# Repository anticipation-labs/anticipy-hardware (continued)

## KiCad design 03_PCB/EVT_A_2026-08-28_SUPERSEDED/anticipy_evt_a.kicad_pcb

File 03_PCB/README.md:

# 03 — PCB

**NOTHING IN THIS FOLDER MAY BE SENT TO A FABRICATOR AS A PRODUCTION RELEASE.**

There is no released Gerber, ODB++, drill file, pick-and-place or assembly drawing anywhere in
this repository. Three custom boards were started. None were finished. A fourth is specified but
not designed.

## The four revisions

| Folder | Board | State |
|---|---|---|
| `R1_TARGET_NOT_YET_DESIGNED/` | R1 | Empty by design. The brief lives in `../01_CURRENT_TARGET_R1/`. |
| `EVT_A_2026-08-28_SUPERSEDED/` | `anticipy_evt_a`, 37.5 × 14 mm four-layer, **nRF54L15** | Deliberate fabrication hold: 0 segments, 0 vias, 0 zones. No copper was ever laid, specifically so no misleading Gerbers could exist. Superseded by the R1 brief. |
| `R0B_CHECKPOINT_NOT_FOR_FAB/` | R0B, 45.8 × 18.0 mm four-layer, 0.80 mm | 70 electrical references, 223 pins, **176 connections unrouted**. The master package's headline board. |
| `R0_ROUTING_HISTORY_NOT_FOR_FAB/` | R0 / `ANT-PROD-R0 EVT` | **The furthest-routed board.** 45 of 46 signal nets carry copper. 31 commits of history (v21 → v43) driving unconnected nets from 199 down to 23 non-GND. |

## Read this before touching R0

`R0_ROUTING_HISTORY_NOT_FOR_FAB/` contains a **live `.git` repository with no remote**. Its 31
commits are the only version-controlled hardware history found on the machine, and they existed
nowhere else before this consolidation. It also carries uncommitted changes to `.kicad_pcb` and
`.kicad_pro`, plus an untracked `tools/final_build.py`. These were preserved exactly as found.

It includes `tools/route_board.py` — a purpose-written negotiated-congestion autorouter. That is
weeks of work and it exists only here.

## The R0 ambiguity

There are **two different files both called the R0 board**:

| | Master package copy | This git repository |
|---|---|---|
| `.kicad_pcb` sha256 | `64a4931f0fc455cd…` | `c086bae9fedc9a55…` |
| DRC timestamp | 2026-08-30 02:28:59 | 2026-08-29 18:04:35 |
| DRC violations | 134 | 4 |

The master package's copy was generated later by an automated run (its DRC header references a
sandbox path) and is **less** routed. Establish which is canonical before anyone uploads "R0"
anywhere — especially given the live JLCPCB order, whose email record does not prove which
revision was uploaded.

## Ordering note

`R0` is *more* complete than `R0B`, despite the naming. Either R0B discarded R0's routing work
or the master package's framing is wrong. Nothing on disk explains which.

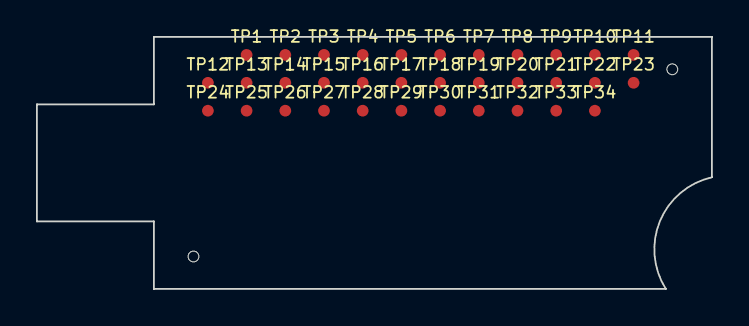
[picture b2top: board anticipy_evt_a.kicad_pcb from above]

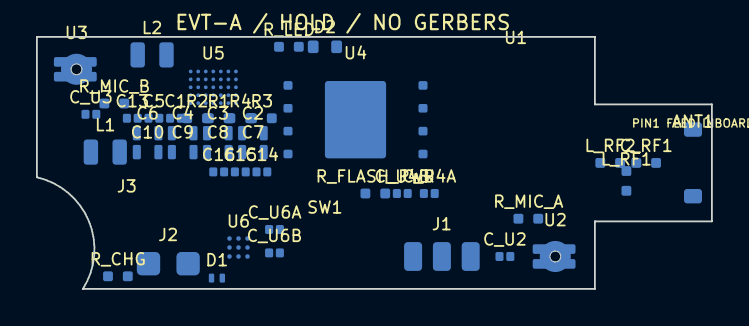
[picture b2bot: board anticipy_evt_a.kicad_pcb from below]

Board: 4 copper layers, 37.5 x 14.0 mm, 81 parts (47 on the bottom side), 38 nets, no tracks yet.

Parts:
ANT1: 2450AT18A0100001E
C1: 1uF/25V; C_OPEN
C2, C3, C4, C7, C8, C9, C10: 10uF; C_OPEN
C5: 1uF; C_OPEN
C6: 2.2uF EMK107BB7225KA-T; C_OPEN
C13: 100nF; C_OPEN
C14, C15, C16: 100nF C0402C104M4RAC7867; C_OPEN
C_RF1: DNP/TUNE (eval 1.0pF); 0402_RF
C_U2, C_U3, C_U4A: 100nF; C_OPEN
C_U4B: 1uF; C_OPEN
C_U6A: 1uF REG; C_OPEN
C_U6B: 1uF VDD; C_OPEN
D1: TPD1E10B06DPYR; X1SON2_DPY
D2: LED MPN OPEN; LED_1608_OPEN
J1: BAT-ANT-200-001 3-wire; BATTERY_WIRE_PADS
J2: MAGNETIC POGO 5V; CHARGE_PADS
J3: JYC720FDRL FPC hot-bar land gate; JYC720FDRL_HOTBAR_LAND_GATE
L1, L2: 2.2uH CIGT201610EH2R2MNE; CIGT201610
L_RF1: DNP/TUNE (eval 2.7nH); 0402_RF
L_RF2: DNP/TUNE (eval 3.9nH); 0402_RF
R1, R2: 10k; R_0402_OPEN
R3: 47k; R_0402_OPEN
R4: 150k; R_0402_OPEN
R_CHG: 0R; R_0402_OPEN
R_FLASH_PWR: 0R; R_0402_OPEN
R_LED: OPEN; R_0402_OPEN
R_MIC_A: 0R; R_0402_OPEN
R_MIC_B: 0R; R_0402_OPEN
SW1: SKSCLCE010; SKSCLCE010_PADMAP_GATE
TP1: GND; TP_0P65
TP2: CHG_5V; TP_0P65
TP3: VBUS; TP_0P65
TP4: VBAT; TP_0P65
TP5: BAT_NTC; TP_0P65
TP6: VSYS; TP_0P65
TP7: 1V8; TP_0P65
TP8: 3V0; TP_0P65
TP9: FLASH_VDD; TP_0P65
TP10: QSPI_CS_TO_U1_PAD_TBD; TP_0P65
TP11: QSPI_CLK_TO_U1_PAD_TBD; TP_0P65
TP12: QSPI_IO0_TO_U1_PAD_TBD; TP_0P65
TP13: QSPI_IO1_TO_U1_PAD_TBD; TP_0P65
TP14: QSPI_IO2_TO_U1_PAD_TBD; TP_0P65
TP15: QSPI_IO3_TO_U1_PAD_TBD; TP_0P65
TP16: PDM_CLK_TO_U1_PAD_TBD; TP_0P65
TP17: PDM_DATA_TO_U1_PAD_TBD; TP_0P65
TP18: MIC_A_VDD; TP_0P65
TP19: MIC_B_VDD; TP_0P65
TP20: PMIC_SDA_TO_U1_PAD_TBD; TP_0P65
TP21: PMIC_SCL_TO_U1_PAD_TBD; TP_0P65
TP22: HAPTIC_SDA_TO_U1_PAD_TBD; TP_0P65
TP23: HAPTIC_SCL_TO_U1_PAD_TBD; TP_0P65
TP24: HAPTIC_EN_TO_U1_PAD_TBD; TP_0P65
TP25: HAPTIC_REG; TP_0P65
TP26: HAPTIC_OUT_P; TP_0P65
TP27: HAPTIC_OUT_M; TP_0P65
TP28: BUTTON_TO_U1_PAD_TBD; TP_0P65
TP29: STATUS_LED_TO_U1_PAD_TBD; TP_0P65
TP30: SWDIO_TO_U1_PAD_TBD; TP_0P65
TP31: SWCLK_TO_U1_PAD_TBD; TP_0P65
TP32: RESET_TO_U1_PAD_TBD; TP_0P65
TP33: UART_TX_TO_U1_PAD_TBD; TP_0P65
TP34: UART_RX_TO_U1_PAD_TBD; TP_0P65
U1: 453-00224R; BL54L15U_PINMAP_GATE
U2, U3: IM69D128S
U4: W25N04KVZEIR; WSON8_8x6_W25N04KV
U5: nPM1300-CAAA; WLCSP35_nPM1300_CAAA
U6: DRV2605LYZFR; DSBGA9_DRV2605L

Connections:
1V8: C7.1, L1.2, TP7.1, U5.B4, U5.B6
3V0: C8.1, C13.1, C_U6B.1, L2.2, R1.1, R2.1, R_FLASH_PWR.1, R_MIC_A.1, R_MIC_B.1, TP8.1, U3.4, U5.B5, U5.C6, U5.E4, U6.C2
BAT_NTC: J1.2, TP5.1, U5.D3
CHG_5V: D1.1, J2.1, R_CHG.1, TP2.1
FLASH_VDD: C_U4A.1, C_U4B.1, R_FLASH_PWR.2, TP9.1, U4.8
GND: C1.2, C2.2, C3.2, C4.2, C5.2, C6.2, C7.2, C8.2, C9.2, C10.2, C13.2, C14.2, C15.2, C16.2, C_U2.2, C_U3.2, C_U4A.2, C_U4B.2, C_U6A.2, C_U6B.2, D1.2, D2.2, J1.3, J2.2, L_RF1.2, R3.2, R4.2, TP1.1, U2.4, U2.5, U3.5, U4.4, U4.9, U5.A6, U5.A7, U5.E7, U6.B1, U6.B3
HAPTIC_EN_TO_U1_PAD_TBD: TP24.1, U6.A1
HAPTIC_OUT_M: TP27.1, U6.C3
HAPTIC_OUT_P: TP26.1, U6.A3
HAPTIC_REG: C_U6A.1, TP25.1, U6.A2
HAPTIC_SCL_TO_U1_PAD_TBD: TP23.1, U6.C1
HAPTIC_SDA_TO_U1_PAD_TBD: TP22.1, U6.B2
LDO1_OUT: C9.1, U5.A4
LDO2_OUT: C10.1, U5.A5
MIC_A_VDD: C_U2.1, R_MIC_A.2, TP18.1, U2.1
MIC_B_VDD: C_U3.1, R_MIC_B.2, TP19.1, U3.1
PDM_CLK_TO_U1_PAD_TBD: TP16.1, U2.2, U3.2
PDM_DATA_TO_U1_PAD_TBD: TP17.1, U2.3, U3.3
PMIC_SCL_TO_U1_PAD_TBD: R2.2, TP21.1, U5.E3
PMIC_SDA_TO_U1_PAD_TBD: R1.2, TP20.1, U5.E5
QSPI_CLK_TO_U1_PAD_TBD: TP11.1, U4.6
QSPI_CS_TO_U1_PAD_TBD: TP10.1, U4.1
QSPI_IO0_TO_U1_PAD_TBD: TP12.1, U4.5
QSPI_IO1_TO_U1_PAD_TBD: TP13.1, U4.2
QSPI_IO2_TO_U1_PAD_TBD: TP14.1, U4.3
QSPI_IO3_TO_U1_PAD_TBD: TP15.1, U4.7
RF_MATCH_A: C_RF1.2, L_RF1.1, L_RF2.1
RF_MATCH_B: ANT1.1, L_RF2.2
STATUS_LED_A: D2.1, R_LED.2
STATUS_LED_TO_U1_PAD_TBD: R_LED.1, TP29.1
SW_BUCK1: L1.1, U5.B7
SW_BUCK2: L2.1, U5.D7
VBAT: C6.1, J1.1, TP4.1, U5.D1, U5.D2
VBUS: C1.1, R_CHG.2, TP3.1, U5.B1, U5.B2
VBUSOUT: C5.1, U5.C3
VSET1: R3.1, U5.E2
VSET2: R4.1, U5.E1
VSYS: C2.1, C3.1, C4.1, C14.1, C15.1, C16.1, TP6.1, U5.C1, U5.C2, U5.C7

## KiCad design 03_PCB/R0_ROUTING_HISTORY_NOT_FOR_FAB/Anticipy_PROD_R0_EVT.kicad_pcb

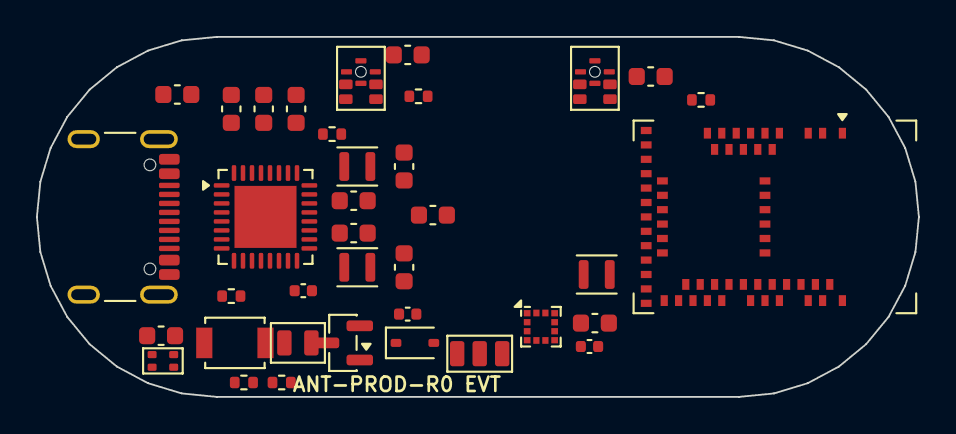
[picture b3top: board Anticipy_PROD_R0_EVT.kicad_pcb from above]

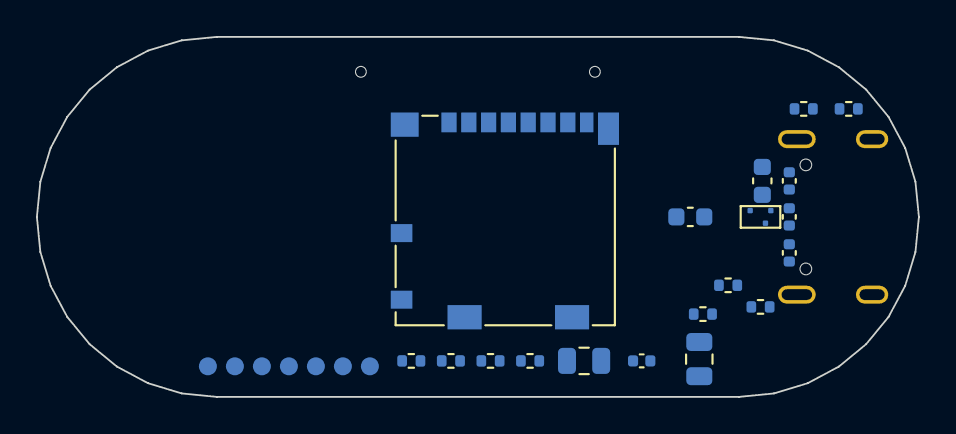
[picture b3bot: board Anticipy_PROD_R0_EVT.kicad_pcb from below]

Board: 4 copper layers, 49.0 x 20.0 mm, 63 parts (26 on the bottom side), 47 nets, no tracks yet.

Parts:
BT1: LiPo_1S_PROTECTED_NTC
C1: 1uF 16V X7R; C_0603_1608Metric
C2, C3, C4, C7, C8, C9, C10, C11, C12: 10uF 10V X5R; C_0603_1608Metric
C5: 1uF 10V X7R; C_0603_1608Metric
C6: 2.2uF 16V X7R EMK107BB7225KA-T; C_0603_1608Metric
C13: 100nF 6.3V X7R; C_0402_1005Metric
C14, C15, C16: 100nF 6.3V X7R C0402C104M4RAC7867; C_0402_1005Metric
C17, C18: 1uF MIC BYPASS; C_0603_1608Metric
C19: 10uF MCU BULK; C_0603_1608Metric
C20: 100nF ACC BYPASS; C_0402_1005Metric
C21: 47uF SD BULK; C_0805_2012Metric
C22: 100nF SD BYPASS; C_0402_1005Metric
C23: 100nF MOTOR; C_0402_1005Metric
C24: 47uF MOTOR BULK; C_0805_2012Metric
D1: 1N4148W-HF; D_SOD-323
J1: USB4105-GF-A; USB_C_Receptacle_GCT_USB4105-xx-A_16P_TopMnt_Horizontal
J2: 104031-0811; microSD_HC_Molex_104031-0811
L1, L2: 2.2uH CIGT201610EH2R2MNE; L_Murata_DFE201610P
L3: 10uH MLZ2012N100LT000; L_Murata_DFE201610P
LED1: APHB1608LVBDSEKJ3C
M1: VCLP1020B002L
MIC1, MIC2: IM69D128SV01XTMA1
Q1: AO3400A; SOT-23
R1, R2: 10k I2C; R_0402_1005Metric
R3: 330k 1% BUCK1=2.7V START; R_0402_1005Metric
R4: 150k 1% BUCK2=3.0V; R_0402_1005Metric
R5: 5.1k USB CC1; R_0402_1005Metric
R6: 5.1k USB CC2; R_0402_1005Metric
R7: 100k SD CS PULLUP; R_0402_1005Metric
R8: 22R SD SCK; R_0402_1005Metric
R9: 22R SD MOSI; R_0402_1005Metric
R10: 22R SD MISO; R_0402_1005Metric
R11: 100k BUTTON PULLUP; R_0402_1005Metric
R12: 100R HAPTIC GATE; R_0402_1005Metric
R13: 100k HAPTIC PULLDOWN; R_0402_1005Metric
R14: 100R MIC1 DATA; R_0402_1005Metric
R15: 100R MIC2 DATA; R_0402_1005Metric
SW1: B3U-1000P; SW_SPST_B3U-1000P
TP1: SWDIO
TP2: SWDCLK
TP3: RESET
TP4: 3V_MAIN
TP5: GND
TP6: UART_TX
TP7: UART_RX
U1: MDBT50Q-1MV2; Raytac_MDBT50Q
U2: NPM1300-QEAA-R7; QFN-32-1EP_5x5mm_P0.5mm_EP3.45x3.45mm
U3: LIS2DW12TR; LGA-12_2x2mm_P0.5mm
U4: TPD2EUSB30DRTR

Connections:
3V_MAIN: C7.1, C13.1, C19.1, C20.1, C23.1, C24.1, D1.2, L1.1, L3.2, M1.1, R1.1, R2.1, R11.1, TP4.1, U1.28, U1.30, U2.1, U2.12, U3.2, U3.9, U3.10
3V_MIC: C10.1, C17.1, C18.1, MIC1.1, MIC2.1, MIC2.4, U2.29
3V_SD: C8.1, C21.1, C22.1, J2.4, L2.1, R7.1, U2.32
ACC_INT1: U1.44, U3.12
ACC_INT2: U1.43, U3.11
DCCH: L3.1, U1.31
GND: BT1.3, C1.2, C2.2, C3.2, C4.2, C5.2, C6.2, C7.2, C8.2, C9.2, C10.2, C11.2, C12.2, C13.2, C14.2, C15.2, C16.2, C17.2, C18.2, C19.2, C20.2, C21.2, C22.2, C24.2, J1.A1, J1.A12, J1.B1, J1.B12, J1.SH, J2.6, J2.10, J2.SH, MIC1.4, MIC1.5, MIC2.5, Q1.2, R3.2, R4.2, R5.2, R6.2, R13.2, SW1.2, TP5.1, U1.1, U1.2, U1.15, U1.33, U1.55, U2.2, U2.6, U2.33, U3.3, U3.6, U3.7, U3.8, U4.3
HAPTIC_GATE: Q1.1, R12.2, R13.1
HAPTIC_NEG: C23.2, D1.1, M1.2, Q1.3
HAPTIC_PWM: R12.1, U1.24
I2C_SCL: R1.2, U1.19, U2.14, U3.1
I2C_SDA: R2.2, U1.16, U2.13, U3.4
LDO2_OUT: C12.1, U2.31
LED_BLUE_K: LED1.1, U2.25
LED_RED_K: LED1.3, U2.26
NTC: BT1.2, U2.18
PDM_CLK: MIC1.2, MIC2.2, U1.38
PDM_DATA: R14.2, R15.2, U1.39
PDM_DATA_MIC1: MIC1.3, R14.1
PDM_DATA_MIC2: MIC2.3, R15.1
PMIC_INT: U1.41, U2.7
RESET: TP3.1, U1.40
SD_CS: J2.2, R7.2, U1.27
SD_DETECT: J2.9, U1.45
SD_MISO_CARD: J2.7, R10.1
SD_MISO_MCU: R10.2, U1.29
SD_MOSI_CARD: J2.3, R9.2
SD_MOSI_MCU: R9.1, U1.36
SD_SCK_CARD: J2.5, R8.2
SD_SCK_MCU: R8.1, U1.37
SW1: L1.2, U2.3
SW2: L2.2, U2.5
SWDCLK: TP2.1, U1.53
SWDIO: TP1.1, U1.51
UART_RX: TP7.1, U1.20
UART_TX: TP6.1, U1.21
USB_CC1: J1.A5, R5.1, U2.23
USB_CC2: J1.B5, R6.1, U2.24
USB_D+: J1.A6, J1.B6, U1.35, U4.1
USB_D-: J1.A7, J1.B7, U1.34, U4.2
USER_BTN: R11.2, SW1.1, U1.22, U2.15
VBAT: BT1.1, C6.1, U2.19
VBUS: C1.1, J1.A4, J1.A9, J1.B4, J1.B9, U1.32, U2.21
VBUSOUT: C5.1, U2.22
VSET1: R3.1, U2.17
VSET2: R4.1, U2.16
VSYS: C2.1, C3.1, C4.1, C9.1, C11.1, C14.1, C15.1, C16.1, LED1.2, LED1.4, U2.4, U2.20, U2.28, U2.30

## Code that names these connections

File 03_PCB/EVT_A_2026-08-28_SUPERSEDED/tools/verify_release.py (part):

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    expected_npm = {
        "A1":"PMIC_LED0","A2":"PMIC_LED1","A3":"PMIC_LED2","A4":"LDO1_OUT","A5":"LDO2_OUT","A6":"GND","A7":"GND",
        "B1":"VBUS","B2":"VBUS","B3":"CC2_NC","B4":"1V8","B5":"3V0","B6":"1V8","B7":"SW_BUCK1",
        "C1":"VSYS","C2":"VSYS","C3":"VBUSOUT","C4":"PMIC_GPIO3_TO_U1_PAD_TBD","C5":"PMIC_GPIO2_TO_U1_PAD_TBD","C6":"3V0","C7":"VSYS",
        "D1":"VBAT","D2":"VBAT","D3":"BAT_NTC","D4":"SHPHLD","D5":"CC1_NC","D6":"PMIC_GPIO0_TO_U1_PAD_TBD","D7":"SW_BUCK2",
        "E1":"VSET2","E2":"VSET1","E3":"PMIC_SCL_TO_U1_PAD_TBD","E4":"3V0","E5":"PMIC_SDA_TO_U1_PAD_TBD","E6":"PMIC_GPIO1_TO_U1_PAD_TBD","E7":"GND",
    }
    exact_maps["U5"] = expected_npm
    for ref, expected in exact_maps.items():
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    else:
        failures.append("schematic missing references: " + ", ".join(sorted(required_refs-sch_refs)))
    labels = {x[1] for x in direct(schematic, "label") if len(x) > 1}
    critical_labels = {"VBAT","BAT_NTC","3V0","1V8","GND","FLASH_VDD","HAPTIC_REG",
                       "PDM_CLK_TO_U1_PAD_TBD","PDM_DATA_TO_U1_PAD_TBD",
                       "HAPTIC_OUT_P","HAPTIC_OUT_M","RF_MATCH_B"}
    if critical_labels <= labels:
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
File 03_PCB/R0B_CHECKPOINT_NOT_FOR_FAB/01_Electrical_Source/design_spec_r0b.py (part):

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        p(1,"BUCK1OUT","3V_MAIN","power_out"),p(2,"PVSS1","PVSS1","power_in"),
        p(3,"SW1","SW1","power_out"),p(4,"PVDD1","VSYS","power_in"),
        p(5,"SW2","SW2","power_out"),p(6,"PVSS2","PVSS2","power_in"),
        p(7,"GPIO0","PMIC_INT","bidirectional"),p(8,"GPIO1",None,"bidirectional"),
        p(9,"GPIO2",None,"bidirectional"),p(10,"GPIO3",None,"bidirectional"),
        p(11,"GPIO4",None,"bidirectional"),p(12,"VDDGPIO","3V_MAIN","power_in"),
        p(13,"SDA","I2C_SDA","bidirectional"),p(14,"SCL","I2C_SCL","input"),
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                errors.append(f"{item.ref}: duplicate pin {pin.number}")
            numbers.add(pin.number)
    if RAYTAC_NETS[32] != "VBUSOUT":
        errors.append("U1 pin 32 must use protected VBUSOUT")
    if RAYTAC_NETS[34] != "USB_MCU_D-" or RAYTAC_NETS[35] != "USB_MCU_D+":
        errors.append("U1 USB pins must be behind the 27-ohm series resistors")
    if PART_BY_REF["D1"].pins[0].net != "3V_MAIN":
        errors.append("D1 pad 1/K must connect to 3V_MAIN")
    if PART_BY_REF["SW1"].pins[0].net != "SHPHLD_BTN":
        errors.append("button must connect only to nPM1300 SHPHLD, not MCU")
    if PART_BY_REF["R10"].pins[0].net != "USB_D+" or PART_BY_REF["R10"].pins[1].net != "USB_MCU_D+":
        errors.append("R10 must bridge connector-side USB_D+ to USB_MCU_D+")
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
